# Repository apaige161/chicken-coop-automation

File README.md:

# Automated 50-Bird Chicken Coop

This is a complete, buildable design for a **10 × 20 ft coop for 50 free-ranging hens**:
the structure, run and paddocks, water and power, plus an **ESP32 + ESPHome controller**
that integrates with **Home Assistant**. Every subsystem starts **low-tech**, and the
automation is an upgrade you can add later.

> ⚠️ **Safety and code.** This project includes **120 V mains wiring outdoors** and a
> **load-bearing structure**. The plans are detailed, but they are **not** a substitute for
> a **licensed electrician** (all 120 V work, GFCI protection, inspection) or for your
> **local building department** (permit, setbacks, snow/wind loads). The controller PCB
> itself carries only 12 V DC.

| Feed & water station (filled from outside) | Inside: roosts, nest openings, trough, drinkers |
|---|---|
|  |  |
| **Nest bay (eggs collected from outside)** | **Controller PCB** |
|  |  |

The renders are illustrative OpenSCAD models (`construction/model/`). Dimensions come from
the build plan and drawings.

**Feed, water and eggs are all serviced from outside the coop.** An exterior service station
on the east wall holds a ~350 lb gravity feed bin (it feeds an indoor trough through a wall
slot) and the 30 gal water drum (piped through the wall to the nipple line). The nest bay
lid opens from outside.

## What's here

| Folder | Contents | Checked by |
|---|---|---|
| [`PROJECT_SPEC.md`](PROJECT_SPEC.md) | Architecture, sizing, tiers, power design, **GPIO map** | consistency check |
| [`hardware/pinmap.yaml`](hardware/pinmap.yaml) | Single source of truth for GPIOs and terminals | consistency check |
| [`firmware/`](firmware/) | ESPHome configs: controller + optional ESP32-CAM | `esphome config` + full compile |
| [`pcb/`](pcb/) | KiCad 10 schematic + 2-layer board, generated from `design.py`, autorouted, Gerbers ready to order | ERC 0 · DRC 0 errors · 0 unrouted · schematic parity |
| [`3d-printing/`](3d-printing/) | 8 OpenSCAD designs → 15 STLs (sensor housings, camera, brackets, PCB plate, optional auger funnel) | `render.sh` |
| [`construction/`](construction/) | Build plan + cut list, exterior feed/water station, wiring, plumbing, run and range, 5 diagrams, 6 renders | diagrams regenerate from `pinmap.yaml` |
| [`docs/`](docs/) | [Priced parts list](docs/parts-list.md), [cost-saving measures](docs/cost-savings.md), [Home Assistant setup](docs/home-assistant.md), HA automations + dashboard | `gen_parts_list.py --check`, yamllint |
| [`tools/`](tools/) | `check_consistency.py`, `gen_parts_list.py` | CI |

## Cost (2026 estimates, see [parts list](docs/parts-list.md))

| Tier | Approx. |
|---|---:|
| Tier 1: coop, run, electric-netting paddocks, exterior feed/water station, power to the coop | ~$9.6k |
| Tier 2: full automation (controller, PCB, door actuator, water fill, sensors) | ~$0.65k |
| Optional: camera, BLE sensors, battery backup, metered auger | ~$0.2k |

The cost-saving measures in [`docs/cost-savings.md`](docs/cost-savings.md) are already applied
(about −$950 net, *after* adding the exterior station). The biggest remaining levers are a
local lumber-package quote (±30 % on lumber) and how much of the ~$900 electrician estimate
you can reduce, for example by digging the trench yourself.

## Tiers at a glance

| Subsystem | Tier 1 (works with no electronics) | Tier 2 (controller) |
|---|---|---|
| Pop door | Guillotine door + rope/pulley | 12 V actuator, on-device sunrise/civil-dusk schedule, reed confirmation, HA alerts |
| Water | 30 gal drum in the exterior station, piped through the wall to nipples. Hose-fill from outside, or a mechanical float valve | Fail-closed solenoid, dual floats, timeout lockout, freeze-aware |
| Winter water | Insulated station + heated waterer on the GFCI outlet | DS18B20-controlled de-icer / heat cable via relay |
| Feed | ~350 lb gravity bin in the exterior station → wall slot → indoor trough, filled from outside | Ultrasonic bin level + low-feed alert. Optional metered auger |
| Light | Switch | Morning supplement to 14 h day length |
| Ventilation | Soffit/ridge/gable/windows (≥ 20 sq ft) | 12 V fan on temp/RH |
| Security | Hardware cloth, buried apron, 2-step latches, electric netting | PIR night-motion alerts, door-open-after-dark alert, optional camera |

## Build order

1. **Plan and permit.** Read `PROJECT_SPEC.md` and `construction/coop-build-plan.md`. Check
   local code, snow/wind loads and setbacks. Get a lumber quote from the cut list.
2. **Site, foundation, floor, walls, roof** (`coop-build-plan.md` §2 steps 1–9).
3. **Predator proofing and openings.** Hardware cloth everywhere, apron, doors, windows,
   nest bay, roosts.
4. **Run and paddocks** (`run-and-fencing.md`).
5. **Exterior feed & water station** (`coop-build-plan.md` §7): gravity feed bin + indoor
   trough, drum + drinker line through the wall, supply chain (`plumbing.md`).
   **Birds can move in now.** Keep them in the run for 1–2 weeks so they learn the coop is home.
6. **Power** (`wiring.md`). The electrician installs the feeder, mains box, lights and GFCI
   receptacle.
7. **Controller:** order the PCB (`pcb/fab/coop-controller-gerbers.zip`), print the parts
   (`3d-printing/stl/`), buy the Tier 2 parts, assemble and bring up the board
   (`pcb/README.md`), flash the firmware and adopt it in HA (`docs/home-assistant.md`).
8. **Commission one subsystem at a time:** door (adjust the reeds, watch a dusk close),
   then water fill, de-icer, feed-level sensor, lights, fan. Import the HA automations and
   dashboard.
9. **Optional:** camera, BLE thermometers, battery backup.

## Verify everything (what CI runs)

```bash
python tools/check_consistency.py      # pin map ↔ firmware ↔ PCB ↔ spec ↔ HA entity IDs ↔ schematic
python tools/gen_parts_list.py --check  # parts list totals are current
python construction/gen_diagrams.py     # diagrams regenerate
esphome config firmware/coop-controller.yaml
bash 3d-printing/render.sh
bash pcb/build.sh                       # needs KiCad 10 + Java + Freerouting: ERC/DRC/fab outputs
```

## Before building: check these by hand

These are the things software checks can't prove:

- [ ] **PCB:** open it in KiCad and review the autorouted layout. Confirm the SRD relay
      pinout on your parts, and your ESP32 board's row spacing (fit J21 for 25.4 mm or
      J22 for 22.86 mm). See `pcb/README.md`.
- [ ] **Firmware:** set your latitude/longitude/timezone and feeding times, and your BLE
      thermometer's MAC (or remove `packages/ble.yaml`).
- [ ] **3D parts:** measure your specific sensors and PVC and adjust the parameters in the `.scad` headers.
- [ ] **Structure:** check rafter size against your local snow load, and pull a permit if needed.
- [ ] **Electrical:** a licensed electrician does all 120 V work, with GFCI on everything.

## Design decisions

- **ESPHome** rather than Arduino/ESP-IDF: it's local-first, integrates natively with
  HA, and each entity is a few lines of YAML, which keeps the upgrade path cheap.
- **KiCad** rather than Eagle: it's free, it's scriptable (the board is generated and
  verified from `pcb/design.py`), and it outputs standard Gerbers for any fab.
- **Mains stays off the PCB.** The relay modules (or SSRs) and PSU sit in a separate
  electrician-installed box. The PCB only drives their 12 V coils/inputs.
- **Service from outside.** Feed, water and egg collection never require entering the coop,
  which cuts labour, spills and biosecurity risk.

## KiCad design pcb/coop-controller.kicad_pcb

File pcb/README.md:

# Coop Controller PCB (KiCad)

This is a 2-layer, all through-hole carrier board for an **ESP32-DevKitC-32E**. It has 12 V
input protection, a 5 V regulator, a 2-relay H-bridge for the pop-door actuator, five
low-side MOSFET outputs, conditioned sensor inputs, and screw terminals for all field
wiring. **It carries 12 V DC only.** The 120 V relays/SSRs and PSU live in a separate mains
enclosure (see `construction/wiring.md`).

| | |
|---|---|
| Size | 170 × 105 mm, 4× M3 holes 4 mm from each corner |
| Layers | 2 (1 oz), GND pour both sides, solid pad connections |
| Tracks | Signal 0.25 mm / 0.2 mm clearance. Power nets (`+12V`, `GND`, `M±`, `VALVE-`, `FEEDER-`, `FAN-`, `VIN_*`) 1.5 mm |
| Parts | 75 THT parts, 38 BOM lines (`fab/bom.csv`) |
| Checks | ERC 0 violations. DRC 0 errors, 0 unconnected, 0 schematic-parity issues |

## Files

| File | What it is |
|---|---|
| `design.py` | **The source.** Every part, footprint, pin→net and board position |
| `gen_schematic.py` | Writes `coop-controller.kicad_sch` from `design.py` (labels on every pin) |
| `gen_pcb.py` | Writes `coop-controller.kicad_pcb` + `.kicad_pro` (placement, net classes, outline, keep-out, pours) |
| `route.py` | Autoroutes with Freerouting (retries until 100% routed) and fills the pours |
| `gen_bom.py` | Grouped BOM → `fab/bom.csv` |
| `build.sh` | Runs everything above, plus ERC/DRC and fab exports |
| `fab/coop-controller-gerbers.zip` | **Upload this to the fab** (Gerbers + Excellon drill) |
| `fab/coop-controller-schematic.pdf` | Printable schematic |

The schematic is generated, so it's a netlist-style sheet grouped by function, with net
labels instead of drawn wires. That's deliberate: `tools/check_consistency.py` can prove it
matches `design.py` and the firmware pin map. To change the circuit, edit `design.py` and
run `bash build.sh`. Don't hand-edit the generated files, or the next build will overwrite
your changes.

## Before you order: manual checks

The layout is autorouted and passes DRC, but nobody has looked at it in the KiCad GUI yet.
Open `coop-controller.kicad_pcb` in KiCad and check:

1. **Relay pinout.** `design.py` assumes SRD pins 1 = COM, 2/5 = coil, 3 = NO, 4 = NC
   (KiCad's `SANYOU_SRD_Form_C` symbol). Confirm this on your actual relays with a
   meter before soldering.
2. **ESP32 fit.** Measure your dev board. Official Espressif DevKitC rows are 25.4 mm apart
   (fit **J21**). Many clones are 22.86 mm (fit **J22** instead). Fit only one of the two.
   Make sure the USB connector sits at the bottom (J20/J21 pin 19 end) and the antenna
   overhangs the "NO COPPER" keep-out.
3. **Terminal-block orientation.** Wire entries should face the board edges.
4. **Track routing.** Look over the Freerouting result: power-track widths, sensible
   paths, no long GND detours.
5. Run **Inspect → Design Rules Checker** once in the GUI.

## Ordering (JLCPCB / PCBWay / OSH Park)

1. Upload `fab/coop-controller-gerbers.zip`.
2. Settings: 2 layers, 1.6 mm FR-4, 1 oz copper, HASL (lead-free) or ENIG, any mask colour.
   Minimum track/space on this board is 0.25/0.2 mm, which every hobby fab handles.
3. Expect roughly **$15–30 for 5 boards** plus shipping, since it's over 100×100 mm.
4. The parts are all through-hole and commonly stocked, so hand-solder them from
   `fab/bom.csv` (Digi-Key/Mouser/LCSC). Prices are in `docs/parts-list.md`.

## Assembly order

Solder low to high: resistors, diodes, small caps, TO-92 transistors, then the pin
header/sockets (use a spare dev board to hold the sockets straight), TO-220 MOSFETs,
electrolytics, fuse holder, regulator, relays and terminal blocks last.

**Bring-up before plugging in the ESP32:**
1. Apply 12 V from a current-limited bench supply (limit to about 200 mA). Check that
   D9 lights, 5 V is on J10 pin 1, and nothing gets warm.
2. Check reverse polarity: swap the leads briefly. Nothing should happen, because D1
   blocks it.
3. Fit the ESP32, flash `firmware/coop-controller.yaml` over USB, then test each output
   from the ESPHome web UI with nothing connected. Listen for the relay clicks and check
   that the MOSFET drains pull low.

## Circuit notes

- **Door H-bridge:** K1/K2 SPDT. NC→GND, NO→+12 V, COM→motor lead. Both relays off (or
  both on) shorts the motor to itself, which brakes it. Shoot-through is impossible by
  construction. See the truth table in `PROJECT_SPEC.md`.
- **Low-side outputs:** IRLZ44N (or IRLB8721) logic-level FETs with 100 Ω gate and 100 kΩ
  pull-down resistors, so outputs stay OFF while the ESP32 boots. 1N5822 flyback diodes
  protect against the valve/motor/fan inductance. 2N7000 FETs drive the relay coils (1N4148
  flyback) and the J6 outputs for the mains-box relay-module coils (~20 mA; use modules with
  a built-in suppression diode) or SSR inputs (~10 mA). J5 (FEEDER) is only used by the
  optional metered auger.
- **Inputs:** 10 kΩ pull-ups to 3.3 V plus a 100 nF cap on every long-wire input. The PIR
  has a 10 kΩ pull-down. The JSN-SR04T 5 V echo goes through a 1 k/2 k divider.
- **VIN sense:** 100 k/22 k divider into GPIO36. The firmware multiplies by 5.545.
- **Protection:** 5 A slow-blow fuse, SB560 series Schottky (reverse polarity), and a
  P6KE15CA TVS across +12 V.

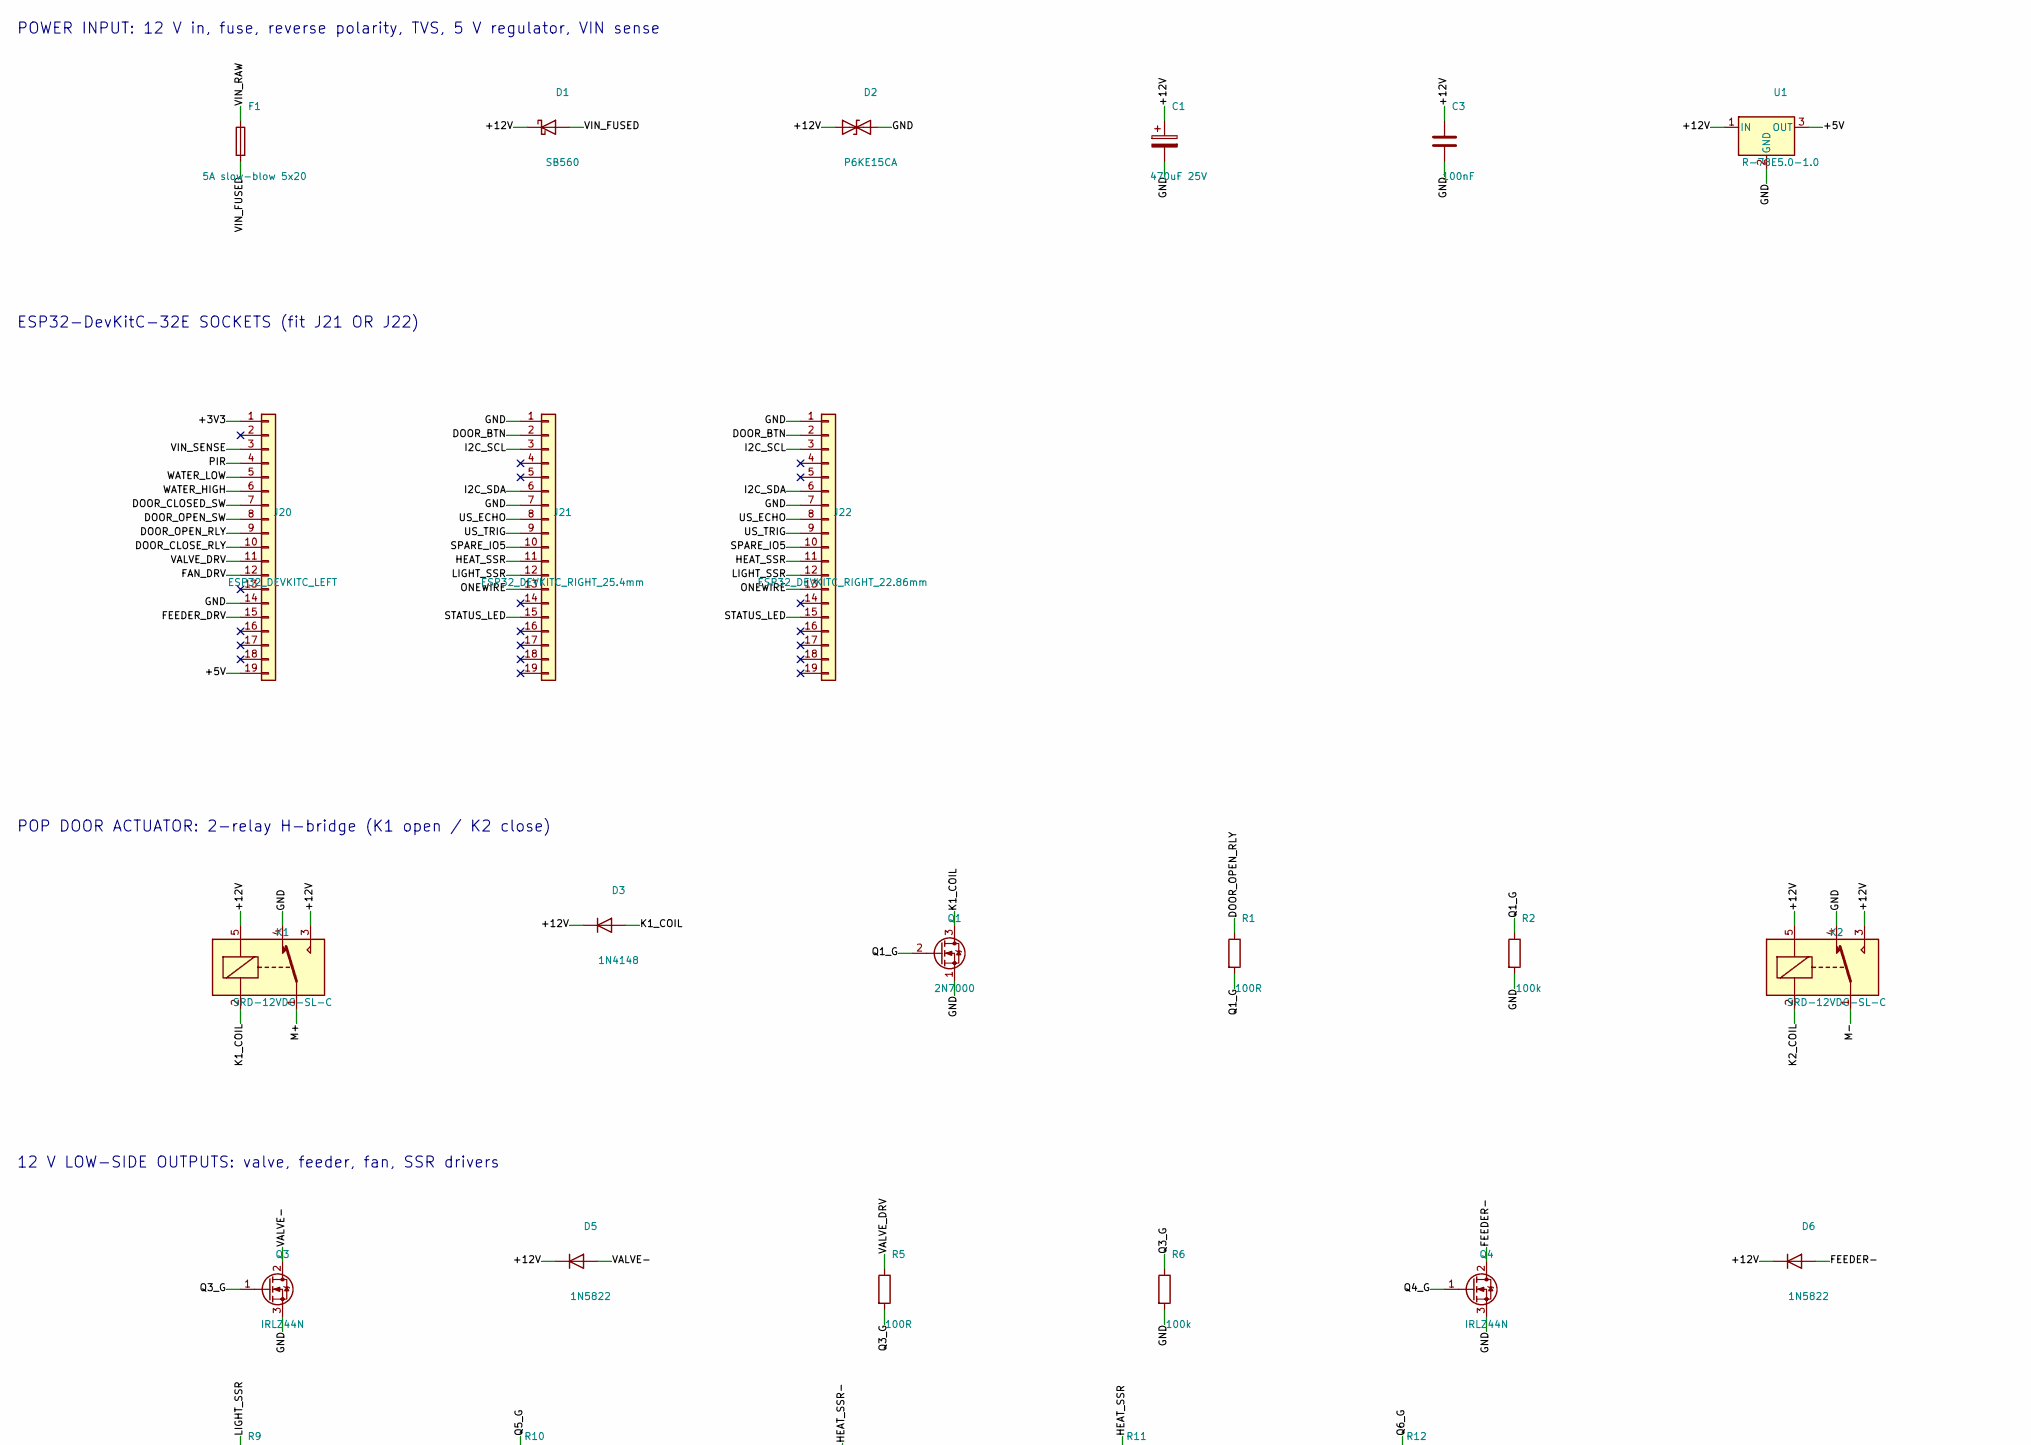
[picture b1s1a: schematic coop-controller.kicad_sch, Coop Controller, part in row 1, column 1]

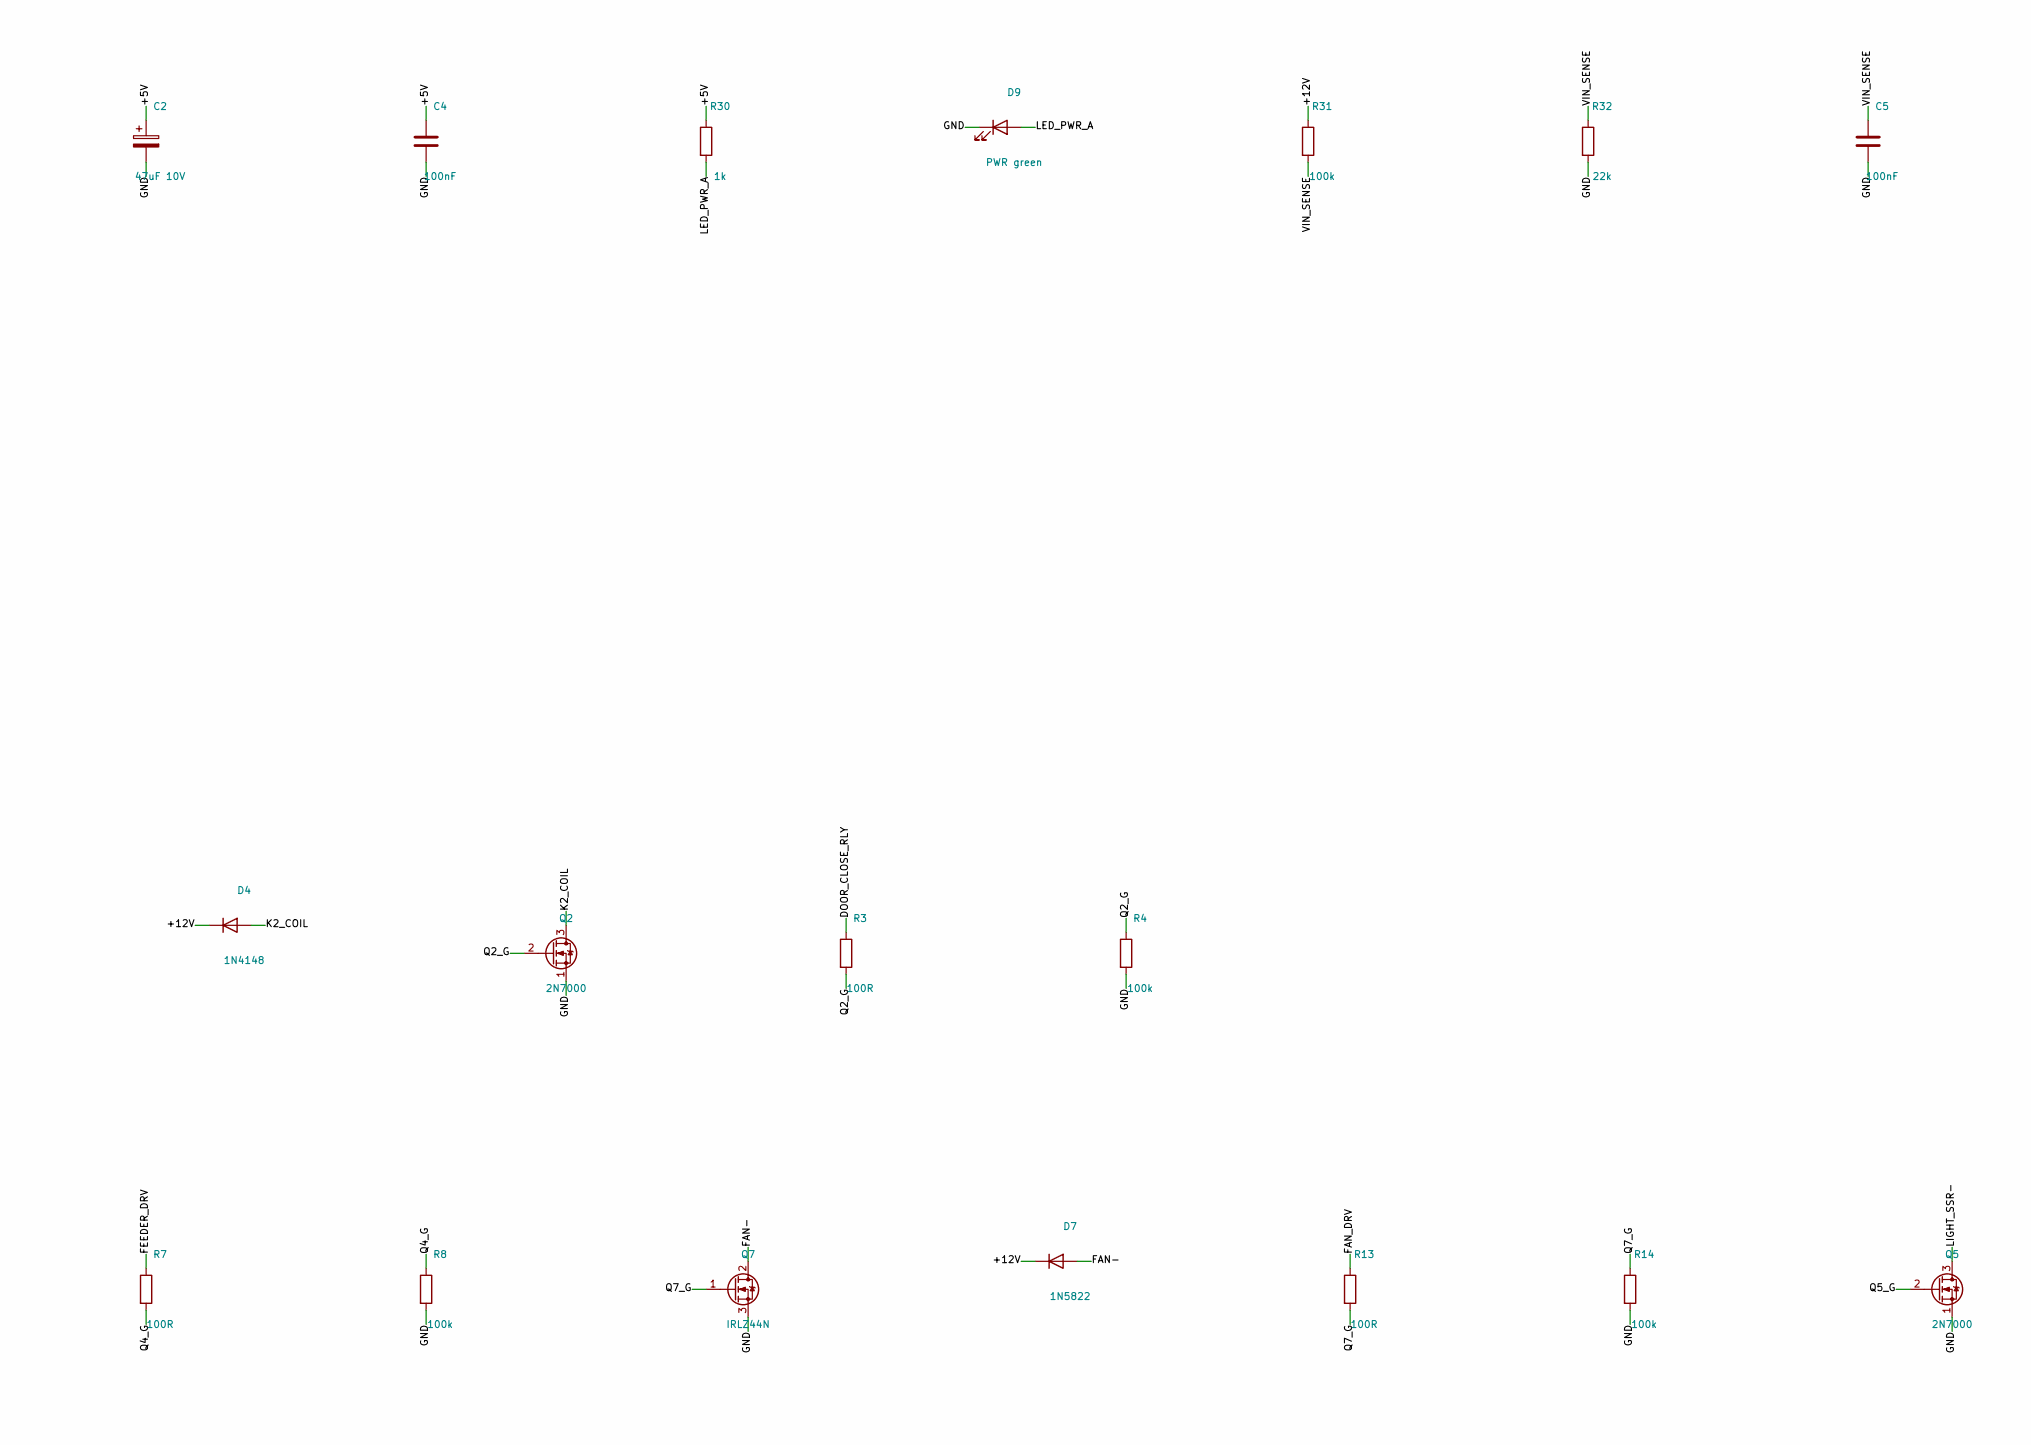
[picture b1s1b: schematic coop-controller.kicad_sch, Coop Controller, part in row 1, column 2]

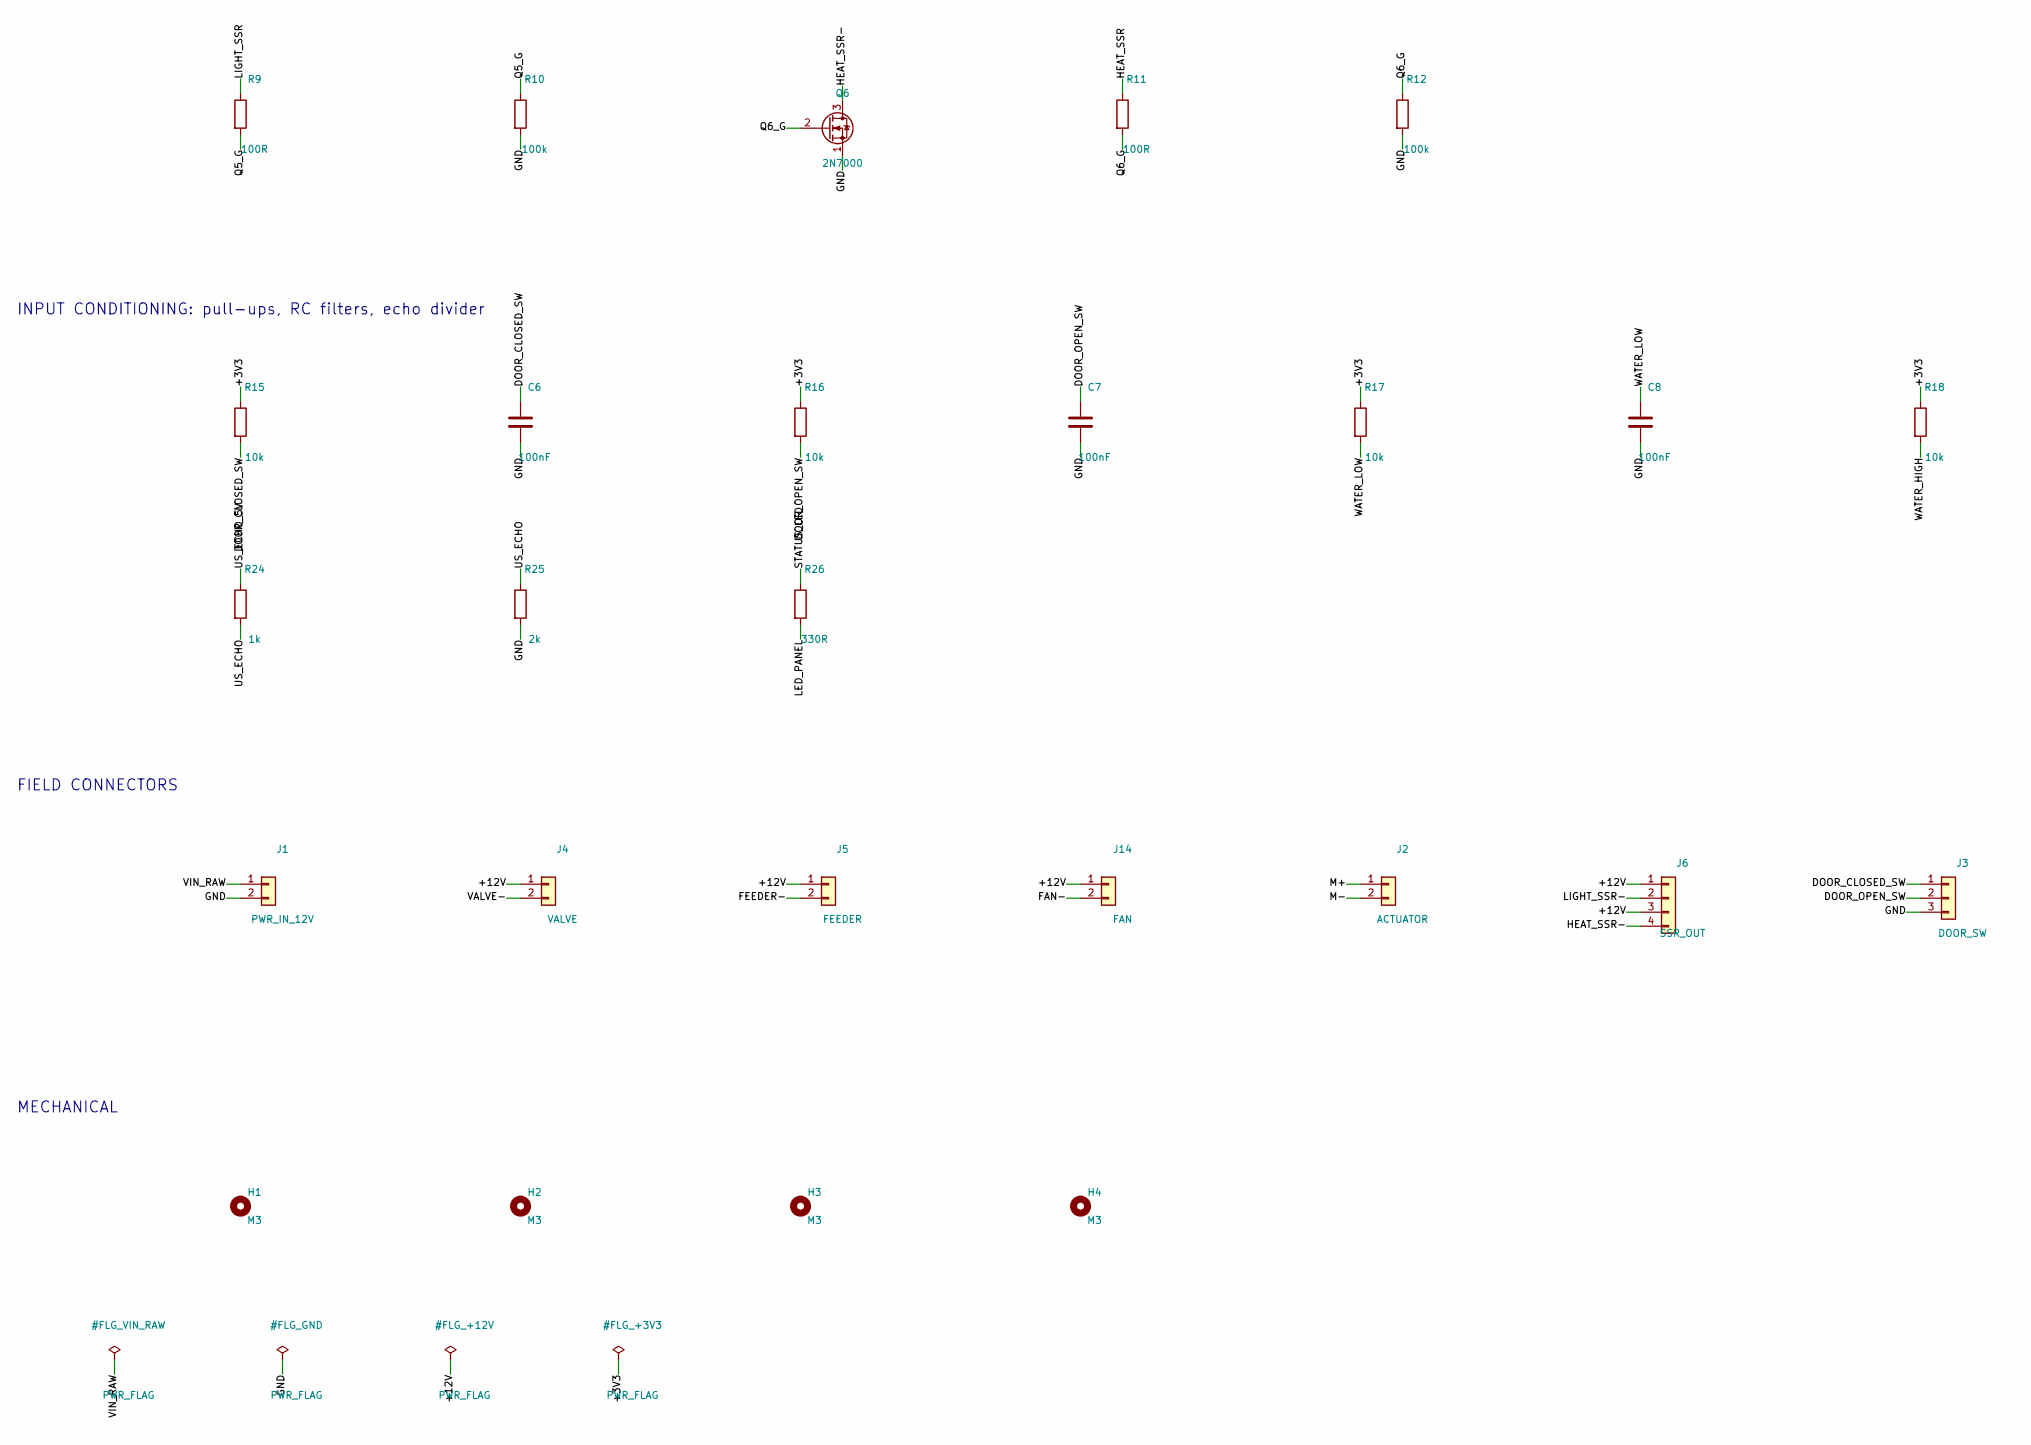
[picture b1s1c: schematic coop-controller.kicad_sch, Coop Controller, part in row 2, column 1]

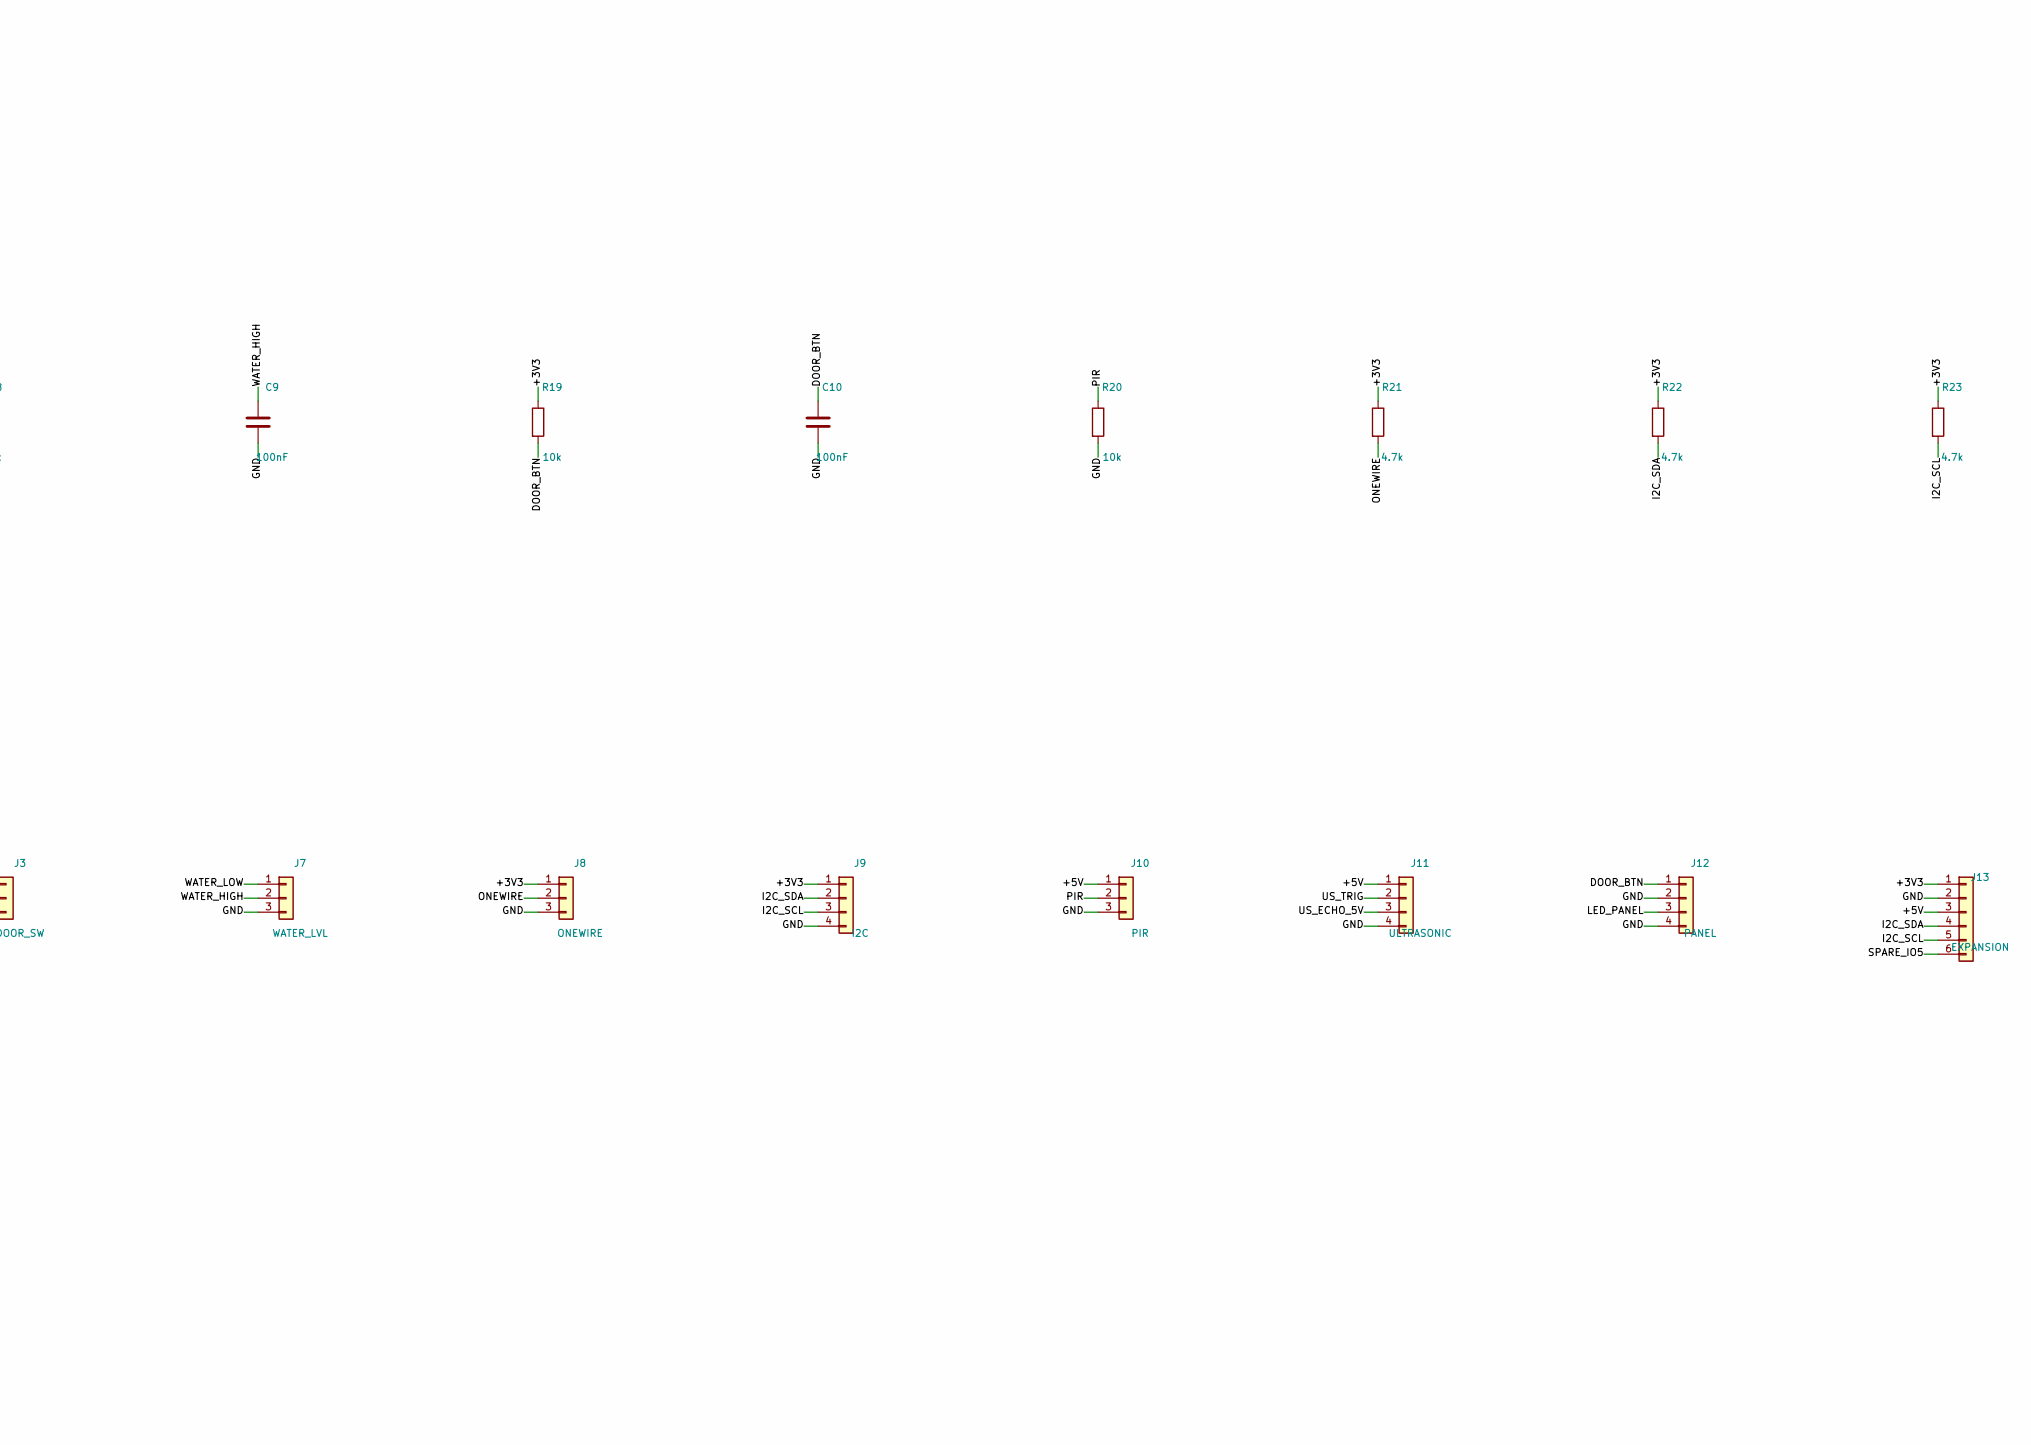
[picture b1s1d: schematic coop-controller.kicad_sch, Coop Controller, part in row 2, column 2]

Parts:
C1: 470uF 25V; CP_Radial_D10.0mm_P5.00mm
C2: 47uF 10V; CP_Radial_D6.3mm_P2.50mm
C3, C4, C5, C6, C7, C8, C9, C10: 100nF; C_Disc_D5.0mm_W2.5mm_P5.00mm
D1: SB560; D_DO-201AD_P15.24mm_Horizontal
D2: P6KE15CA; D_DO-15_P10.16mm_Horizontal
D3, D4: 1N4148; D_DO-35_SOD27_P7.62mm_Horizontal
D5, D6, D7: 1N5822; D_DO-201AD_P15.24mm_Horizontal
D9: PWR green; LED_D3.0mm
F1: 5A slow-blow 5x20; Fuseholder_Cylinder-5x20mm_Schurter_0031_8201_Horizontal_Op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
H1, H2, H3, H4: M3; MountingHole_3.2mm_M3
J1: PWR_IN_12V; TerminalBlock_Phoenix_MKDS-1,5-2-5.08_1x02_P5.08mm_Horizont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
J2: ACTUATOR; TerminalBlock_Phoenix_MKDS-1,5-2-5.08_1x02_P5.08mm_Horizont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
J3: DOOR_SW; TerminalBlock_Phoenix_MKDS-1,5-3-5.08_1x03_P5.08mm_Horizont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
J4: VALVE; TerminalBlock_Phoenix_MKDS-1,5-2-5.08_1x02_P5.08mm_Horizont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
J5: FEEDER; TerminalBlock_Phoenix_MKDS-1,5-2-5.08_1x02_P5.08mm_Horizont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
J6: SSR_OUT; TerminalBlock_Phoenix_MKDS-1,5-4-5.08_1x04_P5.08mm_Horizont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
J7: WATER_LVL; TerminalBlock_Phoenix_MKDS-1,5-3-5.08_1x03_P5.08mm_Horizont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
J8: ONEWIRE; TerminalBlock_Phoenix_MKDS-1,5-3-5.08_1x03_P5.08mm_Horizont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
J9: I2C; TerminalBlock_Phoenix_MKDS-1,5-4-5.08_1x04_P5.08mm_Horizont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
J10: PIR; TerminalBlock_Phoenix_MKDS-1,5-3-5.08_1x03_P5.08mm_Horizont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
J11: ULTRASONIC; TerminalBlock_Phoenix_MKDS-1,5-4-5.08_1x04_P5.08mm_Horizont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
J12: PANEL; TerminalBlock_Phoenix_MKDS-1,5-4-5.08_1x04_P5.08mm_Horizont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
J13: EXPANSION; PinHeader_1x06_P2.54mm_Vertical
J14: FAN; TerminalBlock_Phoenix_MKDS-1,5-2-5.08_1x02_P5.08mm_Horizont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
J20: ESP32_DEVKITC_LEFT; PinSocket_1x19_P2.54mm_Vertical
J21: ESP32_DEVKITC_RIGHT_25.4mm; PinSocket_1x19_P2.54mm_Vertical
J22: ESP32_DEVKITC_RIGHT_22.86mm; PinSocket_1x19_P2.54mm_Vertical
K1, K2: SRD-12VDC-SL-C; Relay_SPDT_SANYOU_SRD_Series_Form_C
Q1, Q2, Q5, Q6: 2N7000; TO-92_Inline_Wide
Q3, Q4, Q7: IRLZ44N; TO-220-3_Vertical
R1, R3, R5, R7, R9, R11, R13: 100R; R_Axial_DIN0207_L6.3mm_D2.5mm_P10.16mm_Horizontal
R2, R4, R6, R8, R10, R12, R14, R31: 100k; R_Axial_DIN0207_L6.3mm_D2.5mm_P10.16mm_Horizontal
R15, R16, R17, R18, R19, R20: 10k; R_Axial_DIN0207_L6.3mm_D2.5mm_P10.16mm_Horizontal
R21, R22, R23: 4.7k; R_Axial_DIN0207_L6.3mm_D2.5mm_P10.16mm_Horizontal
R24, R30: 1k; R_Axial_DIN0207_L6.3mm_D2.5mm_P10.16mm_Horizontal
R25: 2k; R_Axial_DIN0207_L6.3mm_D2.5mm_P10.16mm_Horizontal
R26: 330R; R_Axial_DIN0207_L6.3mm_D2.5mm_P10.16mm_Horizontal
R32: 22k; R_Axial_DIN0207_L6.3mm_D2.5mm_P10.16mm_Horizontal
U1: R-78E5.0-1.0; Converter_DCDC_RECOM_R-78E-0.5_THT

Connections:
+3V3: J8.1, J9.1, J13.1, J20.1, R15.1, R16.1, R17.1, R18.1, R19.1, R21.1, R22.1, R23.1
+5V: C2.1, C4.1, J10.1, J11.1, J13.3, J20.19, R30.1, U1.3 (OUT)
+12V: C1.1, C3.1, D1.1 (K), D2.1 (A1), D3.1 (K), D4.1 (K), D5.1 (K), D6.1 (K), D7.1 (K), J4.1, J5.1, J6.1, J6.3, J14.1, K1.3, K1.5, K2.3, K2.5, R31.1, U1.1 (IN)
DOOR_BTN: C10.1, J12.1, J21.2, J22.2, R19.2
DOOR_CLOSED_SW: C6.1, J3.1, J20.7, R15.2
DOOR_CLOSE_RLY: J20.10, R3.1
DOOR_OPEN_RLY: J20.9, R1.1
DOOR_OPEN_SW: C7.1, J3.2, J20.8, R16.2
FAN-: D7.2 (A), J14.2, Q7.2 (D)
FAN_DRV: J20.12, R13.1
FEEDER-: D6.2 (A), J5.2, Q4.2 (D)
FEEDER_DRV: J20.15, R7.1
GND: C1.2, C2.2, C3.2, C4.2, C5.2, C6.2, C7.2, C8.2, C9.2, C10.2, D2.2 (A2), D9.1 (K), J1.2, J3.3, J7.3, J8.3, J9.4, J10.3, J11.4, J12.2, J12.4, J13.2, J20.14, J21.1, J21.7, J22.1, J22.7, K1.4, K2.4, Q1.1 (S), Q2.1 (S), Q3.3 (S), Q4.3 (S), Q5.1 (S), Q6.1 (S), Q7.3 (S), R2.2, R4.2, R6.2, R8.2, R10.2, R12.2, R14.2, R20.2, R25.2, R32.2, U1.2 (GND)
HEAT_SSR: J21.11, J22.11, R11.1
HEAT_SSR-: J6.4, Q6.3 (D)
I2C_SCL: J9.3, J13.5, J21.3, J22.3, R23.2
I2C_SDA: J9.2, J13.4, J21.6, J22.6, R22.2
K1_COIL: D3.2 (A), K1.2, Q1.3 (D)
K2_COIL: D4.2 (A), K2.2, Q2.3 (D)
LED_PANEL: J12.3, R26.2
LED_PWR_A: D9.2 (A), R30.2
LIGHT_SSR: J21.12, J22.12, R9.1
LIGHT_SSR-: J6.2, Q5.3 (D)
M+: J2.1, K1.1
M-: J2.2, K2.1
ONEWIRE: J8.2, J21.13, J22.13, R21.2
PIR: J10.2, J20.4, R20.1
Q1_G: Q1.2 (G), R1.2, R2.1
Q2_G: Q2.2 (G), R3.2, R4.1
Q3_G: Q3.1 (G), R5.2, R6.1
Q4_G: Q4.1 (G), R7.2, R8.1
Q5_G: Q5.2 (G), R9.2, R10.1
Q6_G: Q6.2 (G), R11.2, R12.1
Q7_G: Q7.1 (G), R13.2, R14.1
SPARE_IO5: J13.6, J21.10, J22.10
STATUS_LED: J21.15, J22.15, R26.1
US_ECHO: J21.8, J22.8, R24.2, R25.1
US_ECHO_5V: J11.3, R24.1
US_TRIG: J11.2, J21.9, J22.9
VALVE-: D5.2 (A), J4.2, Q3.2 (D)
VALVE_DRV: J20.11, R5.1
VIN_FUSED: D1.2 (A), F1.2
VIN_RAW: F1.1, J1.1
VIN_SENSE: C5.1, J20.3, R31.2, R32.1
WATER_HIGH: C9.1, J7.2, J20.6, R18.2
WATER_LOW: C8.1, J7.1, J20.5, R17.2

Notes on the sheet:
POWER INPUT: 12 V in, fuse, reverse polarity, TVS, 5 V regulator, VIN sense
ESP32-DevKitC-32E SOCKETS (fit J21 OR J22)
POP DOOR ACTUATOR: 2-relay H-bridge (K1 open / K2 close)
12 V LOW-SIDE OUTPUTS: valve, feeder, fan, SSR drivers
INPUT CONDITIONING: pull-ups, RC filters, echo divider
FIELD CONNECTORS
MECHANICAL

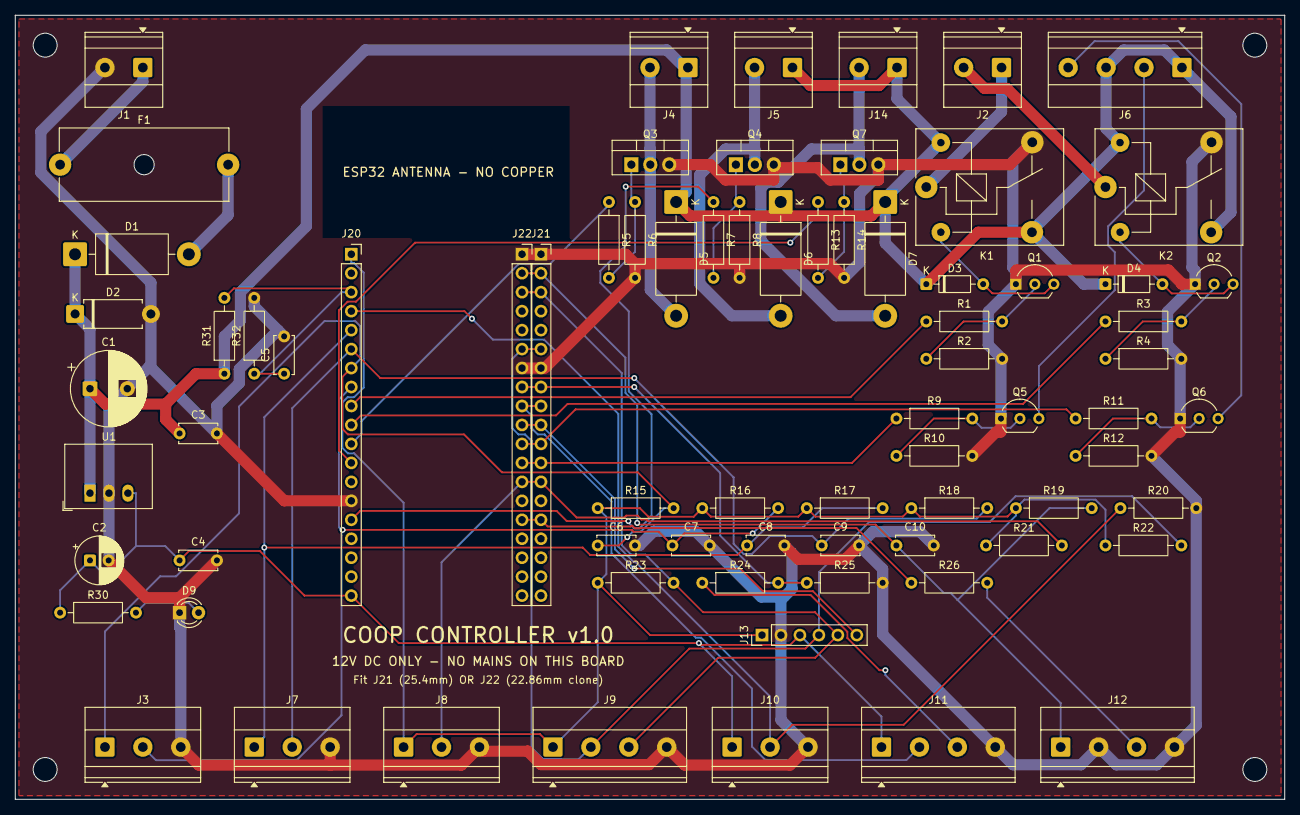
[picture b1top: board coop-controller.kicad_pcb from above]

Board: 2 copper layers, 170.0 x 105.0 mm, 79 parts (0 on the bottom side), 46 nets.

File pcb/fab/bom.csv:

Qty,References,Value,Footprint,Notes
1,C1,470uF 25V,CP_Radial_D10.0mm_P5.00mm,
1,C2,47uF 10V,CP_Radial_D6.3mm_P2.50mm,
8,C3 C4 C5 C6 C7 C8 C9 C10,100nF,C_Disc_D5.0mm_W2.5mm_P5.00mm,
1,D1,SB560,D_DO-201AD_P15.24mm_Horizontal,Reverse-polarity protection
1,D2,P6KE15CA,D_DO-15_P10.16mm_Horizontal,
2,D3 D4,1N4148,D_DO-35_SOD27_P7.62mm_Horizontal,
3,D5 D6 D7,1N5822,D_DO-201AD_P15.24mm_Horizontal,
1,D9,PWR green,LED_D3.0mm,
1,F1,5A slow-blow 5x20,Fuseholder_Cylinder-5x20mm_Schurter_0031_8201_Horizontal_Open,
1,J1,PWR_IN_12V,"TerminalBlock_Phoenix_MKDS-1,5-2-5.08_1x02_P5.08mm_Horizontal",
1,J2,ACTUATOR,"TerminalBlock_Phoenix_MKDS-1,5-2-5.08_1x02_P5.08mm_Horizontal",
1,J3,DOOR_SW,"TerminalBlock_Phoenix_MKDS-1,5-3-5.08_1x03_P5.08mm_Horizontal",
1,J4,VALVE,"TerminalBlock_Phoenix_MKDS-1,5-2-5.08_1x02_P5.08mm_Horizontal",
1,J5,FEEDER,"TerminalBlock_Phoenix_MKDS-1,5-2-5.08_1x02_P5.08mm_Horizontal",
1,J6,SSR_OUT,"TerminalBlock_Phoenix_MKDS-1,5-4-5.08_1x04_P5.08mm_Horizontal",
1,J7,WATER_LVL,"TerminalBlock_Phoenix_MKDS-1,5-3-5.08_1x03_P5.08mm_Horizontal",
1,J8,ONEWIRE,"TerminalBlock_Phoenix_MKDS-1,5-3-5.08_1x03_P5.08mm_Horizontal",
1,J9,I2C,"TerminalBlock_Phoenix_MKDS-1,5-4-5.08_1x04_P5.08mm_Horizontal",
1,J10,PIR,"TerminalBlock_Phoenix_MKDS-1,5-3-5.08_1x03_P5.08mm_Horizontal",
1,J11,ULTRASONIC,"TerminalBlock_Phoenix_MKDS-1,5-4-5.08_1x04_P5.08mm_Horizontal",
1,J12,PANEL,"TerminalBlock_Phoenix_MKDS-1,5-4-5.08_1x04_P5.08mm_Horizontal",
1,J13,EXPANSION,PinHeader_1x06_P2.54mm_Vertical,
1,J14,FAN,"TerminalBlock_Phoenix_MKDS-1,5-2-5.08_1x02_P5.08mm_Horizontal",
1,J20,ESP32_DEVKITC_LEFT,PinSocket_1x19_P2.54mm_Vertical,
1,J21,ESP32_DEVKITC_RIGHT_25.4mm,PinSocket_1x19_P2.54mm_Vertical,Fit for official Espressif DevKitC (25.4 mm rows)
1,J22,ESP32_DEVKITC_RIGHT_22.86mm,PinSocket_1x19_P2.54mm_Vertical,Fit instead of J21 for 22.86 mm clone boards
2,K1 K2,SRD-12VDC-SL-C,Relay_SPDT_SANYOU_SRD_Series_Form_C,
4,Q1 Q2 Q5 Q6,2N7000,TO-92_Inline_Wide,
3,Q3 Q4 Q7,IRLZ44N,TO-220-3_Vertical,Logic-level N-FET; IRLB8721 is a drop-in alternative
7,R1 R3 R5 R7 R9 R11 R13,100R,R_Axial_DIN0207_L6.3mm_D2.5mm_P10.16mm_Horizontal,
8,R2 R4 R6 R8 R10 R12 R14 R31,100k,R_Axial_DIN0207_L6.3mm_D2.5mm_P10.16mm_Horizontal,
6,R15 R16 R17 R18 R19 R20,10k,R_Axial_DIN0207_L6.3mm_D2.5mm_P10.16mm_Horizontal,
3,R21 R22 R23,4.7k,R_Axial_DIN0207_L6.3mm_D2.5mm_P10.16mm_Horizontal,
2,R24 R30,1k,R_Axial_DIN0207_L6.3mm_D2.5mm_P10.16mm_Horizontal,
1,R25,2k,R_Axial_DIN0207_L6.3mm_D2.5mm_P10.16mm_Horizontal,
1,R26,330R,R_Axial_DIN0207_L6.3mm_D2.5mm_P10.16mm_Horizontal,
1,R32,22k,R_Axial_DIN0207_L6.3mm_D2.5mm_P10.16mm_Horizontal,
1,U1,R-78E5.0-1.0,Converter_DCDC_RECOM_R-78E-0.5_THT,"Any 7805-pinout 5 V switching regulator >= 1 A (R-78E5.0-1.0, TSR 1-2450)"

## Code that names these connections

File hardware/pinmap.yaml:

# Single source of truth for controller GPIO + connector assignments.
# Consumed by: tools/check_consistency.py, pcb/generate.py, docs.
# Board: ESP32-DevKitC-32E (38-pin). Change here first, then regenerate/check.

board: esp32dev
pins:
  - {gpio: 21, signal: I2C_SDA,        dir: io,  connector: J9}
  - {gpio: 22, signal: I2C_SCL,        dir: out, connector: J9}
  - {gpio: 4,  signal: ONEWIRE,        dir: io,  connector: J8}
  - {gpio: 25, signal: DOOR_OPEN_RLY,  dir: out, connector: J2}
  - {gpio: 26, signal: DOOR_CLOSE_RLY, dir: out, connector: J2}
  - {gpio: 32, signal: DOOR_CLOSED_SW, dir: in,  connector: J3}
  - {gpio: 33, signal: DOOR_OPEN_SW,   dir: in,  connector: J3}
  - {gpio: 27, signal: VALVE_DRV,      dir: out, connector: J4}
  - {gpio: 13, signal: FEEDER_DRV,     dir: out, connector: J5}
  - {gpio: 14, signal: FAN_DRV,        dir: out, connector: J14}
  - {gpio: 16, signal: LIGHT_SSR,      dir: out, connector: J6}
  - {gpio: 17, signal: HEAT_SSR,       dir: out, connector: J6}
  - {gpio: 34, signal: WATER_LOW,      dir: in,  connector: J7}
  - {gpio: 35, signal: WATER_HIGH,     dir: in,  connector: J7}
  - {gpio: 39, signal: PIR,            dir: in,  connector: J10}
  - {gpio: 18, signal: US_TRIG,        dir: out, connector: J11}
  - {gpio: 19, signal: US_ECHO,        dir: in,  connector: J11}
  - {gpio: 23, signal: DOOR_BTN,       dir: in,  connector: J12}
  - {gpio: 2,  signal: STATUS_LED,     dir: out, connector: J12}
  - {gpio: 36, signal: VIN_SENSE,      dir: adc, connector: null}
  - {gpio: 5,  signal: SPARE_IO5,      dir: io,  connector: J13}

connectors:
  J1:  {name: PWR_IN,     pins: ["VIN_RAW", "GND"]}   # VIN_RAW = +12 V in, before fuse/diode
  J2:  {name: ACTUATOR,   pins: ["M+", "M-"]}
  J3:  {name: DOOR_SW,    pins: ["DOOR_CLOSED_SW", "DOOR_OPEN_SW", "GND"]}
  J4:  {name: VALVE,      pins: ["+12V", "VALVE-"]}
  J5:  {name: FEEDER,     pins: ["+12V", "FEEDER-"]}
  J6:  {name: SSR_OUT,    pins: ["+12V", "LIGHT_SSR-", "+12V", "HEAT_SSR-"]}
  J7:  {name: WATER_LVL,  pins: ["WATER_LOW", "WATER_HIGH", "GND"]}
  J8:  {name: ONEWIRE,    pins: ["+3V3", "ONEWIRE", "GND"]}
  J9:  {name: I2C,        pins: ["+3V3", "I2C_SDA", "I2C_SCL", "GND"]}
  J10: {name: PIR,        pins: ["+5V", "PIR", "GND"]}
  J11: {name: ULTRASONIC, pins: ["+5V", "US_TRIG", "US_ECHO_5V", "GND"]}
  J12: {name: PANEL,      pins: ["DOOR_BTN", "GND", "LED_PANEL", "GND"]}
  J13: {name: EXPANSION,  pins: ["+3V3", "GND", "+5V", "I2C_SDA", "I2C_SCL", "SPARE_IO5"]}
  J14: {name: FAN,        pins: ["+12V", "FAN-"]}
